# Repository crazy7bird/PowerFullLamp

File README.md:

# PowerFullLamp
my bike’s lamp project

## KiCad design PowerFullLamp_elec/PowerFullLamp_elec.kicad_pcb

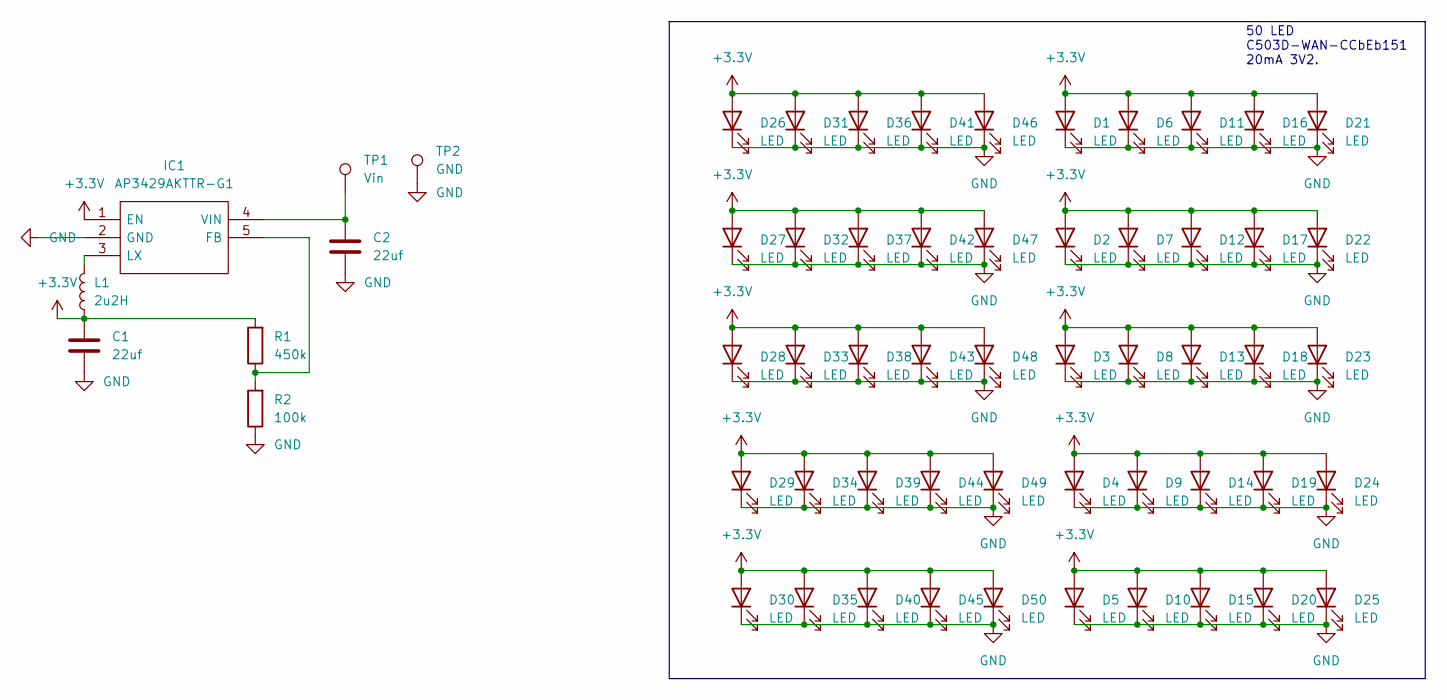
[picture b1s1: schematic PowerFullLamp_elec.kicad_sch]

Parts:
C1, C2: 22uf; C_1206_3216Metric_Pad1.33x1.80mm_HandSolder
D1, D2, D3, D4, D5, D6, D7, D8, D9, D10, D11, D12, D13, D14, D15, D16, D17, D18, D19, D20, D21, D22, D23, D24, D25, D26, D27, D28, D29, D30, D31, D32, D33, D34, D35, D36, D37, D38, D39, D40, D41, D42, D43, D44, D45, D46, D47, D48, D49, D50: LED; LED_D5.0mm
IC1: AP3429AKTTR-G1; SOT95P280X100-5N; Mouser Part Number 621-AP3429AKTTR-G1
L1: 2u2H; L_Wuerth_MAPI-3020
R1: 450k; R_0805_2012Metric
R2: 100k; R_0805_2012Metric
TP1: Vin; TestPoint_THTPad_4.0x4.0mm_Drill2.0mm
TP2: GND; TestPoint_THTPad_4.0x4.0mm_Drill2.0mm

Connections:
+3V3: C1.1, D1.2 (A), D2.2 (A), D3.2 (A), D4.2 (A), D5.2 (A), D6.2 (A), D7.2 (A), D8.2 (A), D9.2 (A), D10.2 (A), D11.2 (A), D12.2 (A), D13.2 (A), D14.2 (A), D15.2 (A), D16.2 (A), D17.2 (A), D18.2 (A), D19.2 (A), D20.2 (A), D21.2 (A), D22.2 (A), D23.2 (A), D24.2 (A), D25.2 (A), D26.2 (A), D27.2 (A), D28.2 (A), D29.2 (A), D30.2 (A), D31.2 (A), D32.2 (A), D33.2 (A), D34.2 (A), D35.2 (A), D36.2 (A), D37.2 (A), D38.2 (A), D39.2 (A), D40.2 (A), D41.2 (A), D42.2 (A), D43.2 (A), D44.2 (A), D45.2 (A), D46.2 (A), D47.2 (A), D48.2 (A), D49.2 (A), D50.2 (A), IC1.1 (EN), L1.1, R1.2
GND: C1.2, C2.2, D1.1 (K), D2.1 (K), D3.1 (K), D4.1 (K), D5.1 (K), D6.1 (K), D7.1 (K), D8.1 (K), D9.1 (K), D10.1 (K), D11.1 (K), D12.1 (K), D13.1 (K), D14.1 (K), D15.1 (K), D16.1 (K), D17.1 (K), D18.1 (K), D19.1 (K), D20.1 (K), D21.1 (K), D22.1 (K), D23.1 (K), D24.1 (K), D25.1 (K), D26.1 (K), D27.1 (K), D28.1 (K), D29.1 (K), D30.1 (K), D31.1 (K), D32.1 (K), D33.1 (K), D34.1 (K), D35.1 (K), D36.1 (K), D37.1 (K), D38.1 (K), D39.1 (K), D40.1 (K), D41.1 (K), D42.1 (K), D43.1 (K), D44.1 (K), D45.1 (K), D46.1 (K), D47.1 (K), D48.1 (K), D49.1 (K), D50.1 (K), IC1.2 (GND), R2.1, TP2.1
unnamed: C2.1, IC1.4 (VIN), TP1.1
unnamed: IC1.3 (LX), L1.2
unnamed: IC1.5 (FB), R1.1, R2.2

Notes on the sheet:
50 LED C503D-WAN-CCbEb151 20mA 3V2.

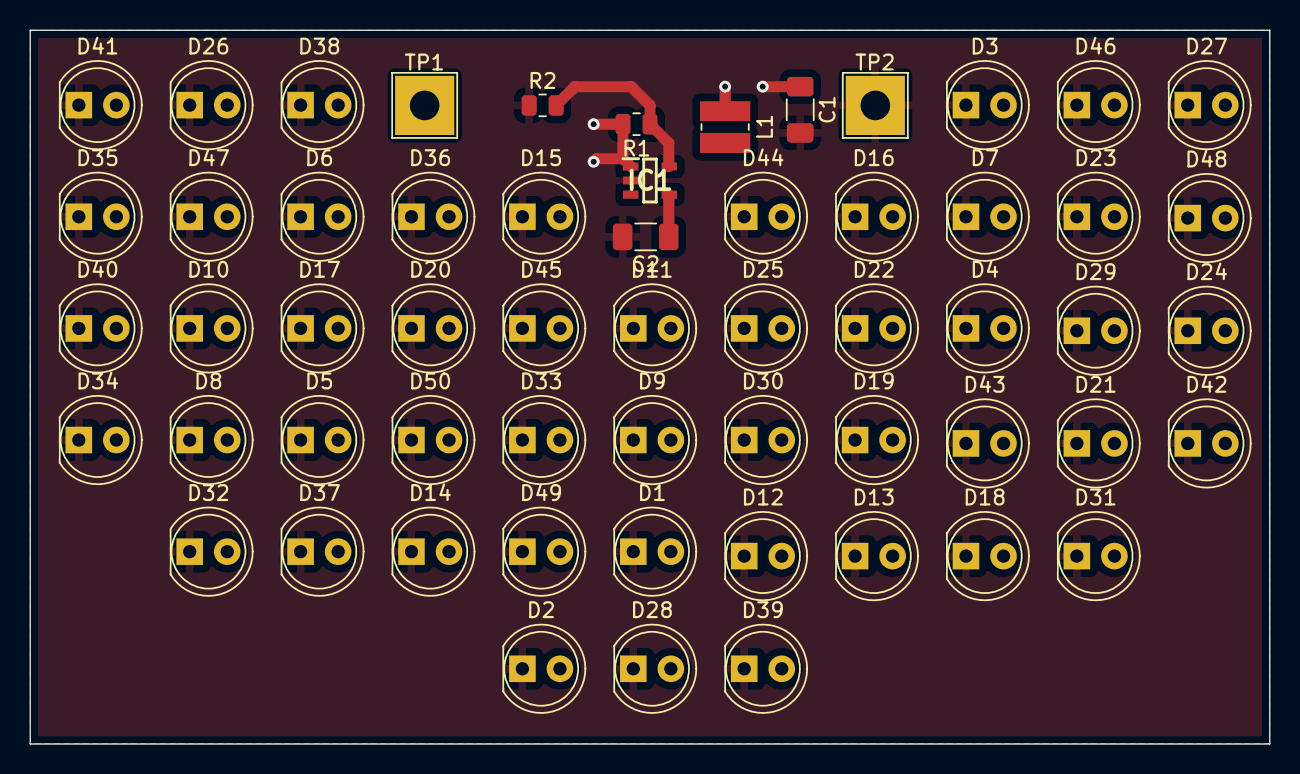
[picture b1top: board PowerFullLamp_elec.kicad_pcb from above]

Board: 2 copper layers, 83.8 x 48.3 mm, 58 parts (0 on the bottom side), 5 nets.

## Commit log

2022-02-17 [WIP] Création du schematic
2022-02-17 WIP trouver self
2022-02-17 WIP routage
